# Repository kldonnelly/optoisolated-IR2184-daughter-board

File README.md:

# optoisolated-IR2184-daughter-board

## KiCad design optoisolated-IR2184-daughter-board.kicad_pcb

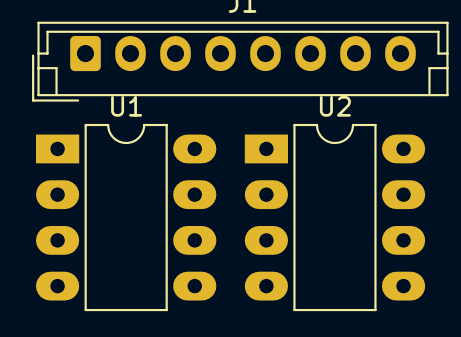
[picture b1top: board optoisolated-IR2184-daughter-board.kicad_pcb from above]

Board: 2 copper layers, 3 parts (0 on the bottom side), 3 nets, no tracks yet.

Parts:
J1: Conn_01x08_Pin; JST_EH_B8B-EH-A_1x08_P2.50mm_Vertical
U1: IR2184; DIP-8_W7.62mm_LongPads
U2: 6N137; DIP-8_W7.62mm_LongPads

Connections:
unnamed: J1.1, U1.5 (VCC)
unnamed: U1.3 (COM), U2.5 (GND)
unnamed: U1.1 (IN), U2.6 (VO)

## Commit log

2025-11-10 place 6n137 ir2184
2025-11-10 update dip packages
2025-11-10 placed most parts
